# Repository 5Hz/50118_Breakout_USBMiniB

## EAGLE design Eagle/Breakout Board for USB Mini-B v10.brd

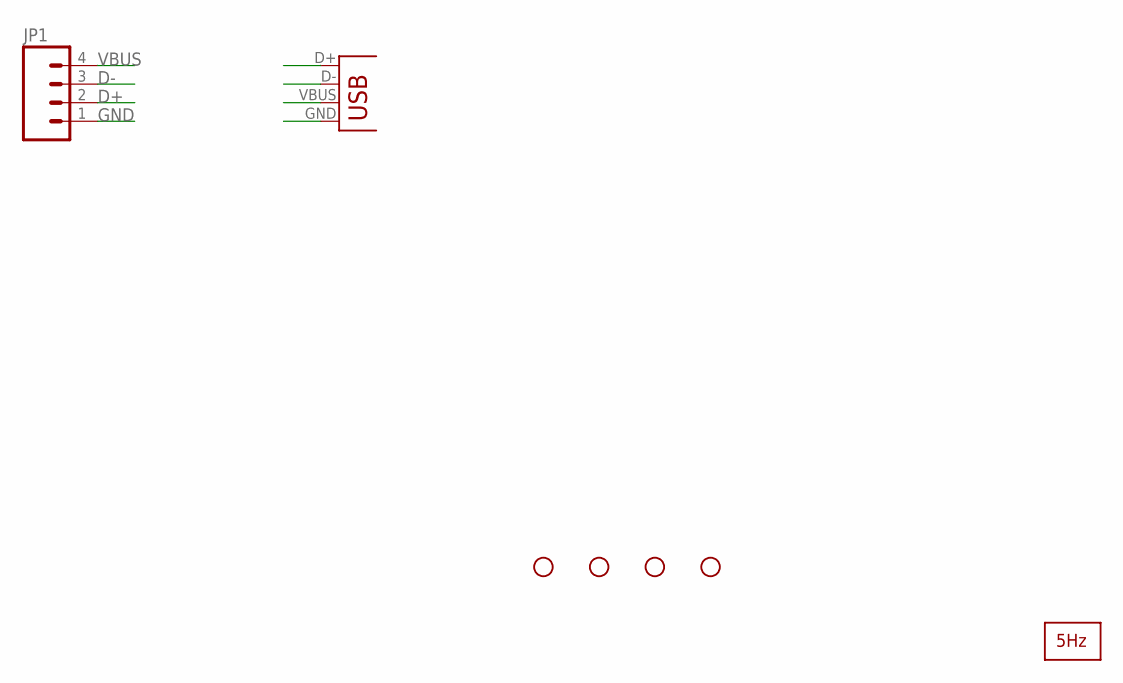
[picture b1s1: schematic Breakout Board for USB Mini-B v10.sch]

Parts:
JP1: M04PTH; 1X04
JP2, JP3, JP4, JP5: STAND-OFF
U$1: LOGO2_SILK5MM; LOGO2_5MM
X2: USBSMD; USB-MINIB

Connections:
D+: JP1.2, X2.D+
D-: JP1.3, X2.D-
GND: JP1.1, X2.GND
VBUS: JP1.4, X2.VBUS

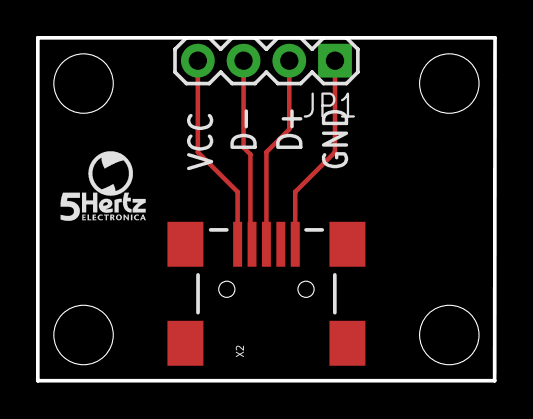
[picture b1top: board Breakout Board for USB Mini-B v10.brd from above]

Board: 2 copper layers, 25.4 x 19.1 mm, 7 parts (0 on the bottom side), 4 nets.

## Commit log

2014-01-14 creación
